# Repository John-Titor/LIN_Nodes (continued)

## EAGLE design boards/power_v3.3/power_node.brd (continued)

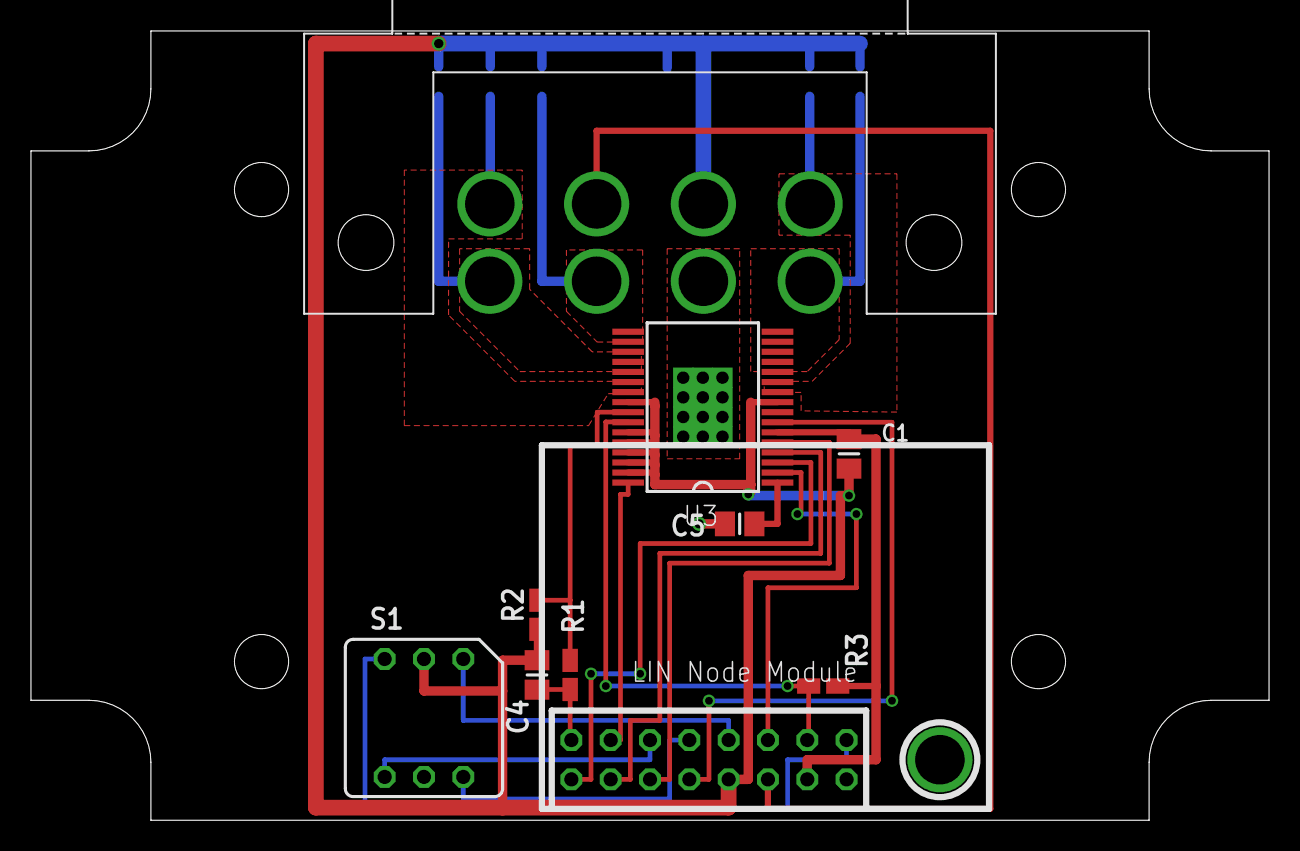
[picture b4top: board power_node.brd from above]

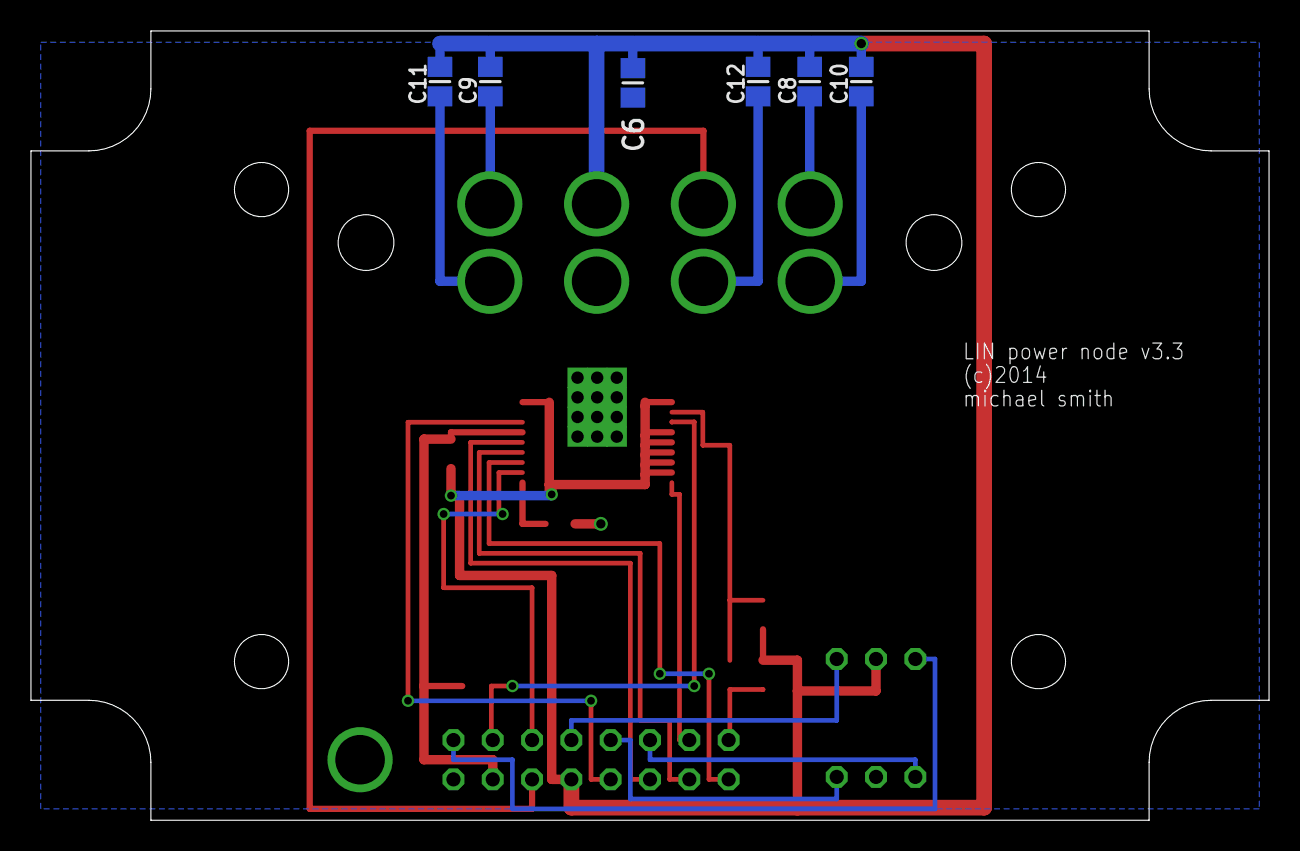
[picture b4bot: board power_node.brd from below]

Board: 2 copper layers, 80.0 x 51.0 mm, 17 parts (6 on the bottom side), 23 nets.

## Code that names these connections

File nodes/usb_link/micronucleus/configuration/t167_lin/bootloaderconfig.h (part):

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 * 
 * Controller type: ATtiny 167 - 16 MHz with crystal
 * Configuration:   Standard configuration
 *       USB D- :   PB6
 *       USB D+ :   PB3
 *       Entry  :   Always
 *       LED    :   None
 *       OSCCAL :   No change due to external crystal
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 *                      external jumper. 
 *                      Adds 34 bytes.
 *
 *       JUMPER_PIN     Pin the jumper is connected to. (e.g. PB0)
 *       JUMPER_PORT    Port out register for the jumper (e.g. PORTB)  
 *       JUMPER_DDR     Port data direction register for the jumper (e.g. DDRB)  
 *       JUMPER_INP     Port inout register for the jumper (e.g. PINB)  
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
#define ENTRYMODE ENTRY_ALWAYS

#define JUMPER_PIN    PB0
#define JUMPER_PORT   PORTB 
#define JUMPER_DDR    DDRB 
#define JUMPER_INP    PINB 
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
#define LED_DDR     DDRA
#define LED_PORT    PORTA
#define LED_PIN     PA3   // was PA6 on the one-off proto board

/*
 *  This is the implementation of the LED code. Change the configuration above unless you want to 
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
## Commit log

2015-04-02 Implement parameter default access and reset.
    Fixes #117
    Fixes #118
2015-04-03 Ignore .pyc files
2015-04-03 Bare skeleton for unit tests & runner
2015-04-04 Initial work for #120
2015-04-04 Update to current sample boards
2015-04-04 Move meta-parameter addresses out of the NCF, since they aren't real parameters
2015-04-04 More machine-readable output
    Fixes #120
2015-04-04 One more for #120
2015-04-04 Remove all references to brake blinking, as it's not a legal behaviour in the USA
2015-04-05 Whitespace
2015-04-05 Truth tables for relay behaviour & updated implementation (untested)
2015-04-05 Truth table simplifications
2015-04-05 Rewrite truth tables & optimise using k-map tool
    Compiled code is bigger, but overall logic is more manageable and
    source flow is less error-prone.
    Used http://sourceforge.net/projects/truthtablesolve/
2015-04-14 Fix some bad python in the test library, make some test tests run
2015-04-25 Updates to LINtool and bootloader for the 'real' v1 probe boards
2017-09-24 toplevel incremental build support
    Add a makefile for the NCF parser so we can build its outputs 'normally'
2017-09-24 code size reduction to make the bootloader fit
2017-09-24 update for new libusb.h pkgconfig output
2017-09-26 sync test WIP
2017-09-27 pull test pieces up to Phidgets22
2017-12-20 fix a race condition during inactivity power-down
    It’s possible that LIN traffic could arrive during power-down, causing
    the transceiver to power back up before the controller shuts down. In
    this case, the ms_delay() loop won’t trigger the watchdog, because
    ms_delay() resets the watchdog every millisecond.
    Instead, request power-down just once, and then dead-loop. Either power
    will go away, or the watchdog will fire after ~500ms and the firmware
2017-12-22 Add missing LIN_protocol_version
2017-12-22 Remove some auto-generated files
2017-12-22 remove bogus attempt at a generic LDF and parser
    Since node configuration is dynamic, it makes no sense to attempt to specify it statically
2019-11-03 Docs for updated 12XS6 series power switches
2019-11-03 Fix json library for modern C++
2019-11-03 soft-programmed node ID for powerv3/v4 boards
2019-11-03 remove defunct dashboard, ecubridge projects
